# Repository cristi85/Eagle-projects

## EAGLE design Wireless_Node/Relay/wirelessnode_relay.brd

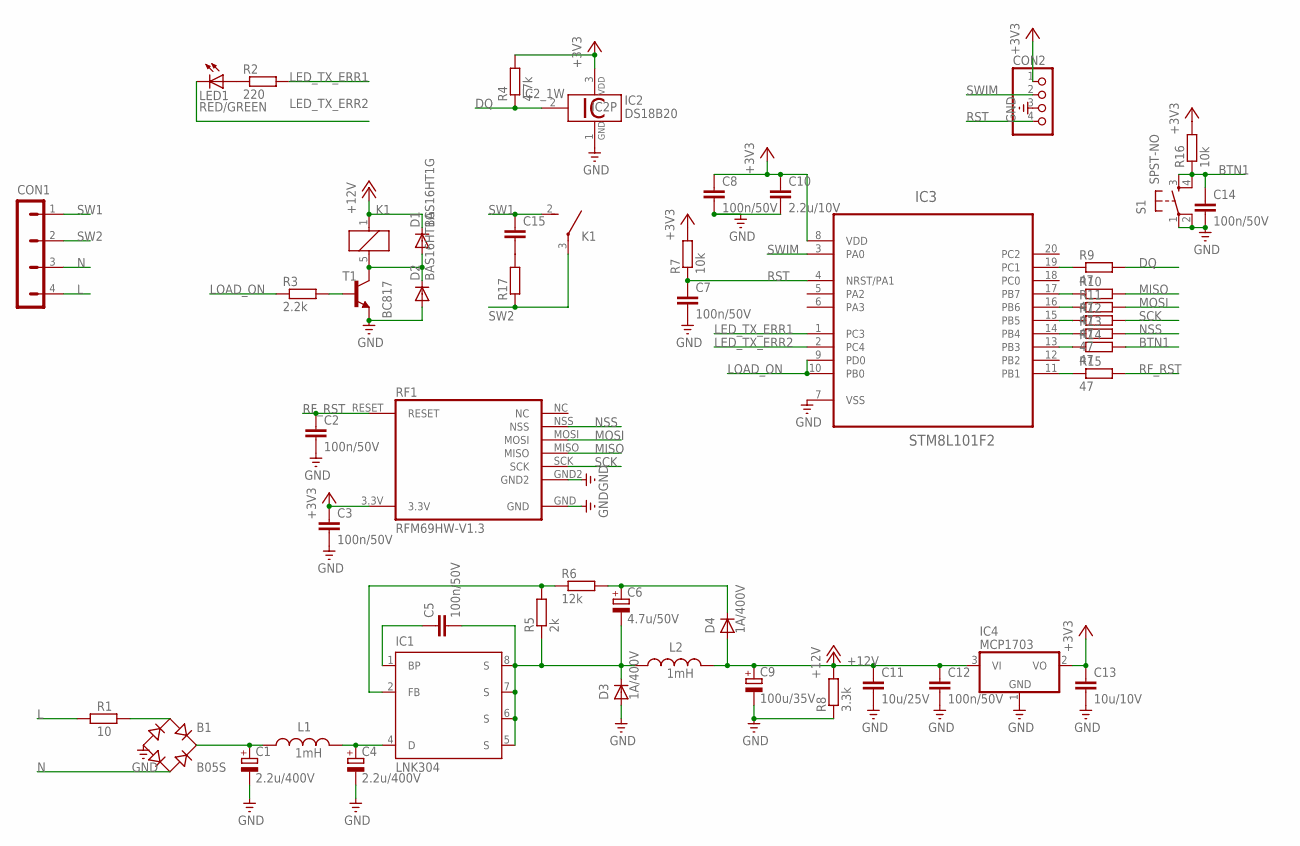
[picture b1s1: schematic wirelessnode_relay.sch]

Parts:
B1: B05S; MBS
C1, C4: 2.2u/400V; E3.5-8
C2, C3, C5, C7, C8, C12, C14: 100n/50V; C0603K
C6: 4.7u/50V; PANASONIC_C_LARGER_PADS
C9: 100u/35V; PANASONIC_D_LARGER_PADS
C10: 2.2u/10V; C0603K
C11: 10u/25V; C1206
C13: 10u/10V; C0603K
C15: C-EUC1812; C1812
CON1: POWER_CONN_4; TERMINAL_BLOCK_4
CON2: ZL321-4P; CON_1X4_1.27_SMD
D1, D2: BAS16HT1G; SOD323-W
D3: 1A/400V; DO214-AC
D4: 1A/400V; SOD-123F
IC1: LNK304; SO8_NO_PIN3
IC2: DS18B20; TO92-
IC3: STM8L101F2; TSSOP20
IC4: MCP1703; SOT23
K1: G5Q-1A4-EU
L1, L2: 1mH; DE0703
LED1: RED/GREEN; LED5MM
R1: 10; CF1WS
R2: 220; R0603
R3: 2.2k; R0603
R4: 4.7k; R0603
R5: 2k; R0603
R6: 12k; R0603
R7, R16: 10k; R0603
R8: 3.3k; R0603
R9, R10, R11, R12, R13, R14, R15: 47; R0603
R17: R-EU_R2010; R2010
RF1: RFM69HW-V1.3; RFM69HW-V1.3-SMD
S1: SPST-NO; DTSM-63X-V-7MM_HEIGHT
T1: BC817; SOT23-BEC

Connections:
+3V3: C3.1, C8.1, C10.1, C13.1, CON2.1, IC2.3 (VDD), IC3.8 (VDD), IC4.2 (VO), R4.2, R7.2, R16.2, RF1.3.3V
+12V: C9.+, C11.1, C12.1, D1.C, D4.2 (A), IC4.3 (VI), K1.1, L2.P$2 (2), R8.2
BTN1: C14.1, R14.2, R16.1, S1.3 (S), S1.4 (S1)
DQ: IC2.2 (1W), R4.1, R9.2
GND: B1.-, C1.-, C2.2, C3.2, C4.-, C7.2, C8.2, C9.-, C10.2, C11.2, C12.2, C13.2, C14.2, CON2.3, D2.A, D3.A, IC2.1 (GND), IC3.7 (VSS), IC4.1 (GND), R8.1, RF1.GND, RF1.GND2, S1.1, S1.2 (P1), T1.E
L: CON1.4, R1.1
LED_TX_ERR1: IC3.1 (PC3), R2.2
LED_TX_ERR2: IC3.2 (PC4), LED1.K (C)
LOAD_ON: IC3.9 (PD0), IC3.10 (PB0), R3.1
MISO: R10.2, RF1.MISO
MOSI: R11.2, RF1.MOSI
N: B1.AC2, CON1.3
unnamed: C4.+, IC1.4 (D), L1.P$2 (2)
unnamed: LED1.A, R2.1
unnamed: C6.+, D4.1 (C), R6.2
unnamed: IC1.2 (FB), R5.2, R6.1
unnamed: C5.1, IC1.1 (BP)
unnamed: C5.2, C6.-, D3.C, IC1.5 (S), IC1.6 (S), IC1.7 (S), IC1.8 (S), L2.P$1 (1), R5.1
unnamed: B1.AC1, R1.2
unnamed: D1.A, D2.C, K1.5 (2), T1.C
unnamed: IC3.14 (PB4), R13.1
unnamed: B1.+, C1.+, L1.P$1 (1)
unnamed: R3.2, T1.B
unnamed: C15.2, R17.2
unnamed: IC3.15 (PB5), R12.1
unnamed: IC3.16 (PB6), R11.1
unnamed: IC3.17 (PB7), R10.1
unnamed: IC3.11 (PB1), R15.1
unnamed: IC3.13 (PB3), R14.1
unnamed: IC3.19 (PC1), R9.1
NSS: R13.2, RF1.NSS
RF_RST: C2.1, R15.2, RF1.RESET
RST: C7.1, CON2.4, IC3.4 (NRST/PA1), R7.1
SCK: R12.2, RF1.SCK
SW1: C15.1, CON1.1, K1.2 (S)
SW2: CON1.2, K1.3, R17.1
SWIM: CON2.2, IC3.3 (PA0)

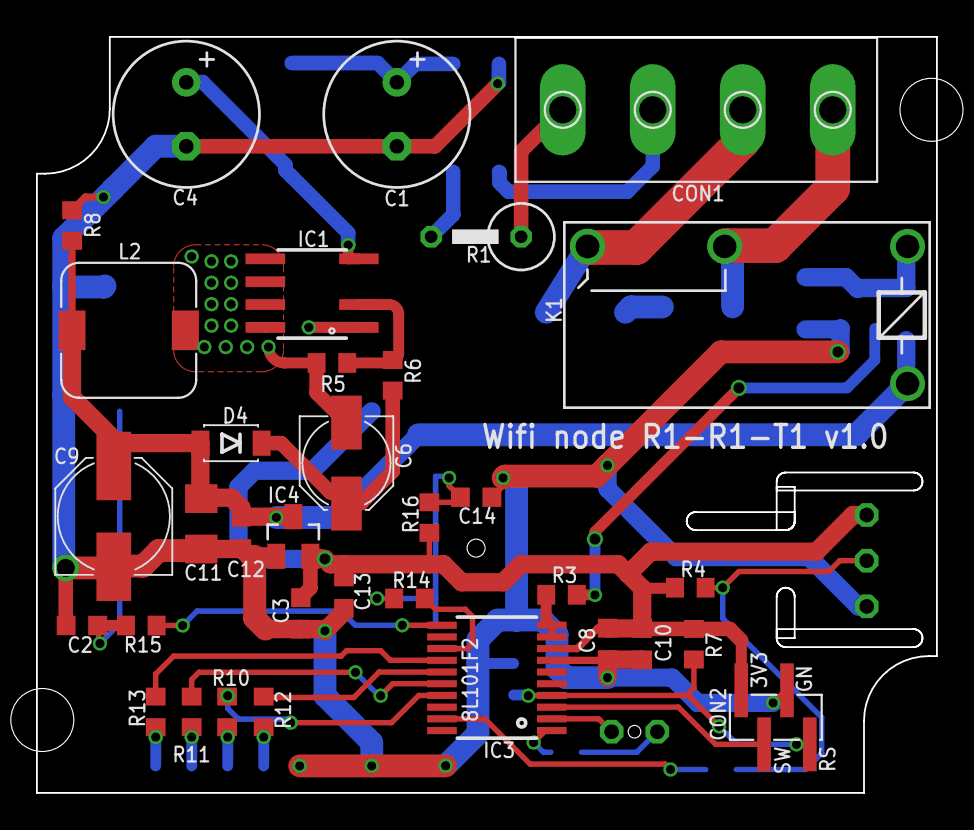
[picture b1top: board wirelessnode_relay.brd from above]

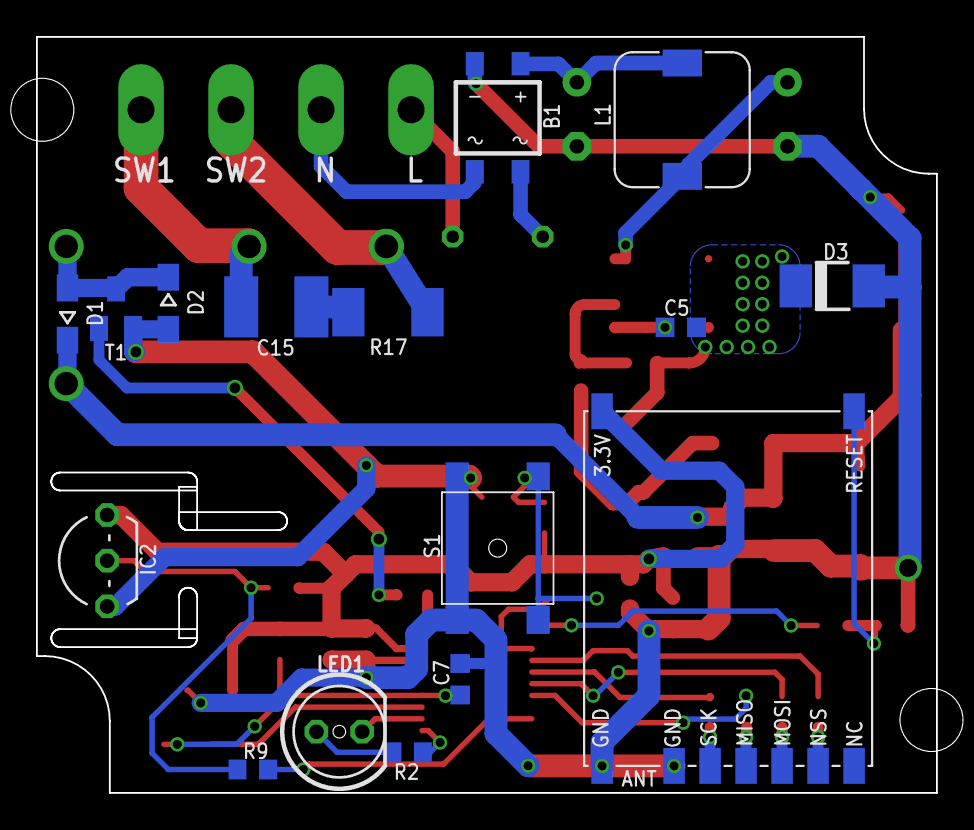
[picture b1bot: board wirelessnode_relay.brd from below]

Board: 2 copper layers, 50.0 x 42.0 mm, 50 parts (16 on the bottom side), 37 nets.

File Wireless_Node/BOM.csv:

"Qty";"Value";"Device";"Package";"Parts";"Description";"MF";"MPN";"OC_FARNELL";"OC_NEWARK";"TME_ORDER_NUMBER";
"1";"";"POWER_CONN_4";"TERMINAL_BLOCK_4";"CON1";"";"";"";"";"";"EBBA-02-C-SS-BU";
"1";"10";"R_CF1WS";"CF1WS";"R1";"";"";"";"";"";"CF1WS-10R";
"7";"100n/50V";"C-EUC0603K";"C0603K";"C2, C3, C5, C7, C8, C12, C14";"CAPACITOR, European symbol";"";"";"";"";"C0603C104K5RAC";
"1";"100u/35V";"C-POL-EUPANASONIC_D";"PANASONIC_D_LARGER_PADS";"C9";"";"";"";"";"";"UCD1V101MCL6GS";
"2";"10k";"R-EU_R0603";"R0603";"R8, R16";"RESISTOR, European symbol";"";"";"";"";"";
"1";"10u/10V";"C-EUC0603K";"C0603K";"C13";"CAPACITOR, European symbol";"";"";"";"";"0603ZD106MAT2A";
"1";"10u/25V";"C-EUC1206";"C1206";"C11";"CAPACITOR, European symbol";"";"";"";"";"08053D106KAT2A";
"2";"1A/400V";"SL1G";"SOD-123F";"D1, D3";"";"";"";"";"";"SL1G-DIO";
"1";"1A/400V";"US1G-DIO";"DO214-AC";"D2";"";"";"";"";"";"US1G-DIO";
"2";"1mH";"FERROCORE_DE0703-1000";"DE0703";"L1, L2";"FERROCORE SMD Power Coil";"";"";"";"";"DE0703-1000";
"1";"2.2u/10V";"C-EUC0603K";"C0603K";"C10";"CAPACITOR, European symbol";"";"";"";"";"CL10A225KP8NNNC";
"1";"2.2u/400V";"C-POL-EUCAP_8X11.5_AIR";"CAP_8X11.5_AIR";"C1";"";"";"";"";"";"RD2G225M0811MBB";
"2";"220";"R-EU_R0603";"R0603";"R2, R3";"RESISTOR, European symbol";"";"";"";"";"";
"1";"2k";"R-EU_R0603";"R0603";"R6";"RESISTOR, European symbol";"";"";"";"";"RC0603FR-072K";
"1";"3.3k";"R-EU_R0603";"R0603";"R9";"RESISTOR, European symbol";"";"";"";"";"RC0603FR-073K3";
"2";"360";"R-EU_R0603";"R0603";"R4, R5";"RESISTOR, European symbol";"";"";"";"";"";
"1";"4.7u/400V";"C-POL-EUE5-10,5";"E5-10,5";"C4";"";"";"";"";"";"RD2G475M1012MBB";
"1";"4.7u/50V";"C-POL-EU";"PANASONIC_C_LARGER_PADS";"C6";"";"";"";"";"";"RC1H475M05005VR";
"6";"47";"R-EU_R0603";"R0603";"R10, R11, R12, R13, R14, R15";"RESISTOR, European symbol";"";"";"";"";"";
"1";"8.6K";"R-EU_R0603";"R0603";"R7";"RESISTOR, European symbol";"";"";"";"";"CRCW06038K66FKTABC ";
"1";"BTA16";"BT136SMD";"TO220_SMD";"T2";"";"";"";"";"";"BTA16-600BRG";
"1";"LNK304";"LNK304";"SO8_NO_PIN3";"IC1";"";"";"";"";"";"LNK304DN";
"1";"MCP1703";"MCP1703CB";"SOT23";"IC3";"250 mA, 16V, Low Quiescent Current LDO Regulator";"";"";"";"";"MCP1703T3302ECB";
"1";"RED/GREEN";"LED5MM";"LED5MM";"LED1";"LED";"";"";"";"";"L-57EGW";
"1";"RFM69HW-V1.3";"RFM69HW-V1.3";"RFM69HW-V1.3-SMD";"RF1";"";"";"";"";"";"RFM69HW-868S2";
"1";"SPST-NO";"DTSM-63X-V";"DTSM-63X-V-7MM_HEIGHT";"S1";"";"";"";"";"";"DTSM-63N-V-B";
"1";"STM8L101F2";"STM8L101F2";"TSSOP20";"IC2";"";"";"";"";"";"STM8L101F2P6";
"1";"VO3063-X007T";"MOC3042S";"DIL6-SMD";"T1";"6-Pin DIP Zero-Cross Optoisolators Triac Driver Output (250/400 Volt Peak)";"FAIRCHILD SEMICONDUCTOR";"MOC3042SM";"unknown";"34C1339";"VO3063-X007T";
"1";"ZL321-4P";"CON_1X4PIN_1.27MM_SMD";"CON_1X4_1.27_SMD";"CON2";"";"";"";"";"";"ZL321-4P (DS1065-01-1X4S8BV)";

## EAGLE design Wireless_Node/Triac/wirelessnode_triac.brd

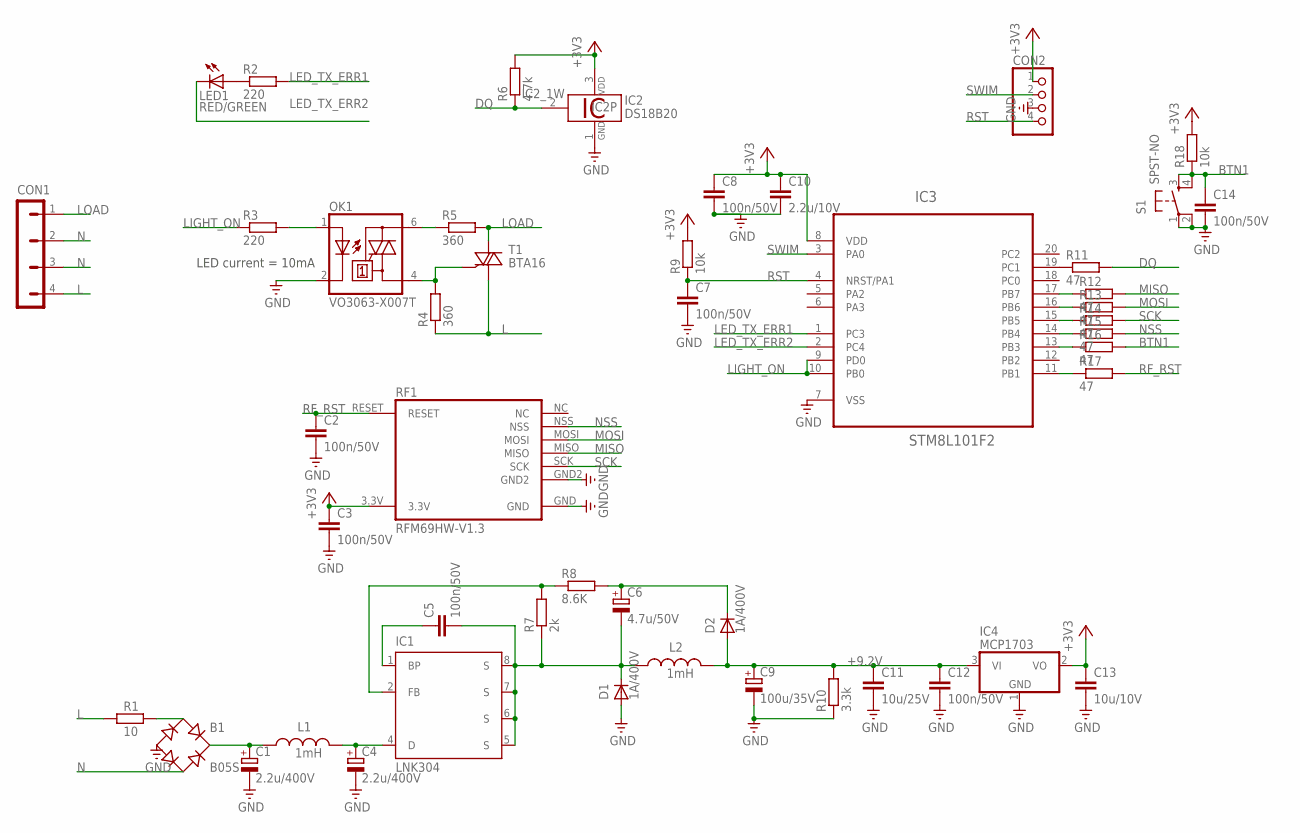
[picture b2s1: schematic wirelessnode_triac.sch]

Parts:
B1: B05S; MBS
C1, C4: 2.2u/400V; E3.5-8
C2, C3, C5, C7, C8, C12, C14: 100n/50V; C0603K
C6: 4.7u/50V; PANASONIC_C_LARGER_PADS
C9: 100u/35V; PANASONIC_D_LARGER_PADS
C10: 2.2u/10V; C0603K
C11: 10u/25V; C1206
C13: 10u/10V; C0603K
CON1: POWER_CONN_4; TERMINAL_BLOCK_4
CON2: ZL321-4P; CON_1X4_1.27_SMD
D1: 1A/400V; DO214-AC
D2: 1A/400V; SOD-123F
IC1: LNK304; SO8_NO_PIN3
IC2: DS18B20; TO92-
IC3: STM8L101F2; TSSOP20
IC4: MCP1703; SOT23
L1, L2: 1mH; DE0703
LED1: RED/GREEN; LED5MM
OK1: VO3063-X007T; DIL6-SMD
R1: 10; CF1WS
R2, R3: 220; R0603
R4, R5: 360; R0603
R6: 4.7k; R0603
R7: 2k; R0603
R8: 8.6K; R0603
R9, R18: 10k; R0603
R10: 3.3k; R0603
R11, R12, R13, R14, R15, R16, R17: 47; R0603
RF1: RFM69HW-V1.3; RFM69HW-V1.3-SMD
S1: SPST-NO; DTSM-63X-V-7MM_HEIGHT
T1: BTA16; TO220_SMD

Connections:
+3V3: C3.1, C8.1, C10.1, C13.1, CON2.1, IC2.3 (VDD), IC3.8 (VDD), IC4.2 (VO), R6.2, R9.2, R18.2, RF1.3.3V
+9.2V: C9.+, C11.1, C12.1, D2.2 (A), IC4.3 (VI), L2.P$2 (2), R10.2
BTN1: C14.1, R16.2, R18.1, S1.3 (S), S1.4 (S1)
DQ: IC2.2 (1W), R6.1, R11.2
GND: B1.-, C1.-, C2.2, C3.2, C4.-, C7.2, C8.2, C9.-, C10.2, C11.2, C12.2, C13.2, C14.2, CON2.3, D1.A, IC2.1 (GND), IC3.7 (VSS), IC4.1 (GND), OK1.2 (C), R10.1, RF1.GND, RF1.GND2, S1.1, S1.2 (P1)
L: CON1.4, R1.1, R4.1, T1.1 (A1)
LED_TX_ERR1: IC3.1 (PC3), R2.2
LED_TX_ERR2: IC3.2 (PC4), LED1.K (C)
LIGHT_ON: IC3.9 (PD0), IC3.10 (PB0), R3.1
LOAD: CON1.1, R5.2, T1.2 (A2)
MISO: R12.2, RF1.MISO
MOSI: R13.2, RF1.MOSI
N: B1.AC2, CON1.2, CON1.3
unnamed: C4.+, IC1.4 (D), L1.P$2 (2)
unnamed: LED1.A, R2.1
unnamed: C6.+, D2.1 (C), R8.2
unnamed: IC1.2 (FB), R7.2, R8.1
unnamed: C5.1, IC1.1 (BP)
unnamed: C5.2, C6.-, D1.C, IC1.5 (S), IC1.6 (S), IC1.7 (S), IC1.8 (S), L2.P$1 (1), R7.1
unnamed: OK1.6 (A2), R5.1
unnamed: OK1.4 (A1), R4.2, T1.3 (G)
unnamed: IC3.14 (PB4), R15.1
unnamed: B1.+, C1.+, L1.P$1 (1)
unnamed: OK1.1 (A), R3.2
unnamed: B1.AC1, R1.2
unnamed: IC3.15 (PB5), R14.1
unnamed: IC3.16 (PB6), R13.1
unnamed: IC3.17 (PB7), R12.1
unnamed: IC3.11 (PB1), R17.1
unnamed: IC3.13 (PB3), R16.1
unnamed: IC3.19 (PC1), R11.1
NSS: R15.2, RF1.NSS
RF_RST: C2.1, R17.2, RF1.RESET
RST: C7.1, CON2.4, IC3.4 (NRST/PA1), R9.1
SCK: R14.2, RF1.SCK
SWIM: CON2.2, IC3.3 (PA0)

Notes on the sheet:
LED current = 10mA

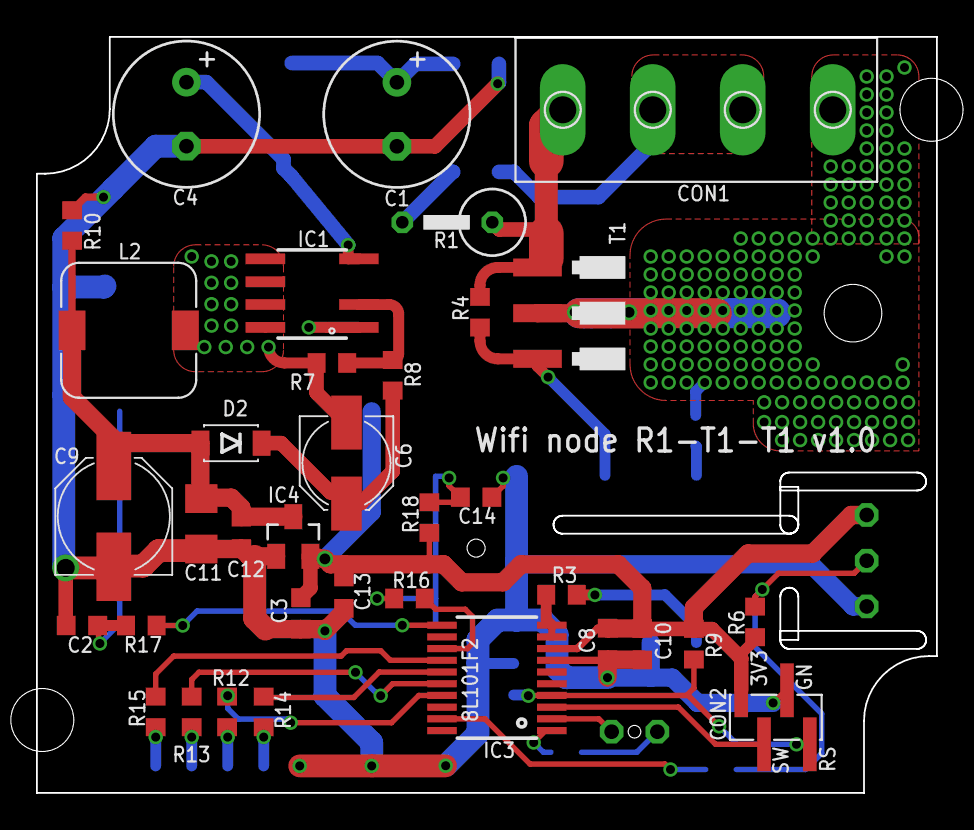
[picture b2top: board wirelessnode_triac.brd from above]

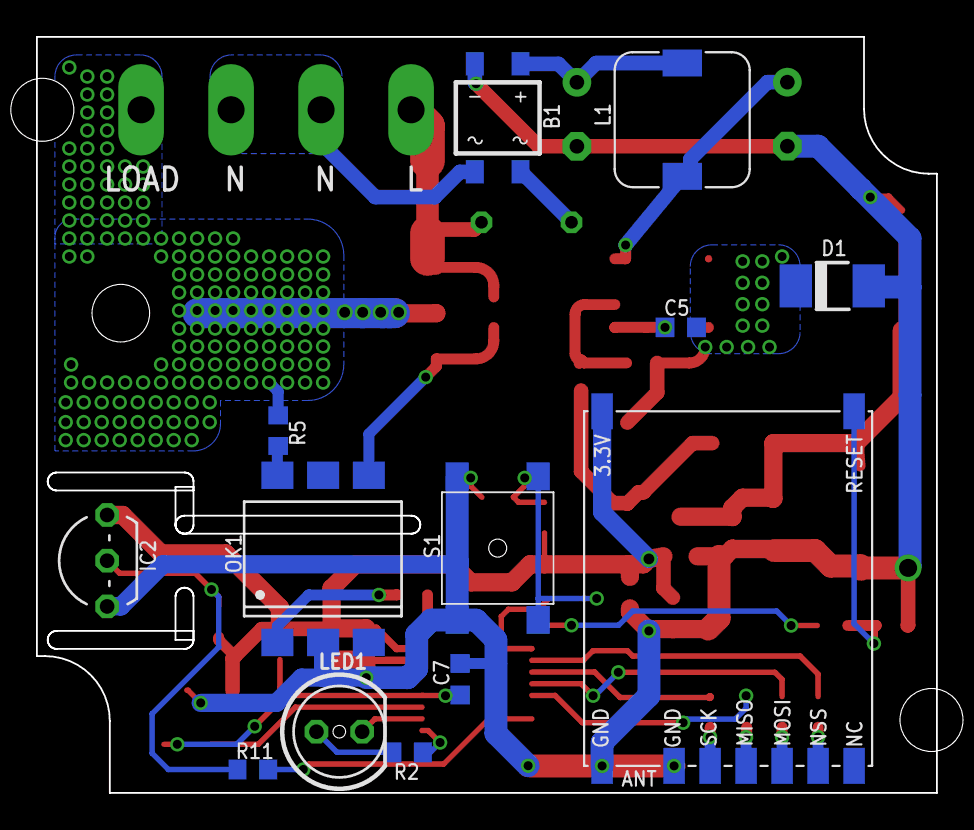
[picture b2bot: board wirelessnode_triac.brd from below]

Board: 2 copper layers, 50.0 x 42.0 mm, 48 parts (13 on the bottom side), 36 nets.

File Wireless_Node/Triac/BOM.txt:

Partlist exported from D:/_WORK/GitHub/Eagle projects/Wireless_Node/wirelessnode.sch at 3/2/2016 4:11 PM

Qty Value        Device                 Package                 Parts                        Description                                                                MF                      MPN       OC_FARNELL OC_NEWARK TME_ORDER_NUMBER            
1                POWER_CONN_4           TERMINAL_BLOCK_4        CON1                                                                                                                                                           EBBA-02-C-SS-BU             
1   10           R_CF1WS                CF1WS                   R1                                                                                                                                                             CF1WS-10R                   
7   100n/50V     C-EUC0603K             C0603K                  C2, C3, C5, C7, C8, C12, C14 CAPACITOR, European symbol                                                                                                        C0603C104K5RAC              
1   100u/35V     C-POL-EUPANASONIC_D    PANASONIC_D_LARGER_PADS C9                                                                                                                                                             UCD1V101MCL6GS              
2   10k          R-EU_R0603             R0603                   R8, R16                      RESISTOR, European symbol                                                                                                                                     
1   10u/25V      C-EUC1206              C1206                   C11                          CAPACITOR, European symbol                                                                                                        08053D106KAT2A              
1   10u/6.3V     C-EUC0603K             C0603K                  C13                          CAPACITOR, European symbol                                                                                                        CL10A106KQ8NNNC             
2   1A/400V      SL1G                   SOD-123F                D1, D3                                                                                                                                                         SL1G-DIO                    
1   1A/400V      US1G-DIO               DO214-AC                D2                                                                                                                                                             US1G-DIO                    
2   1mH          FERROCORE_DE0703-1000  DE0703                  L1, L2                       FERROCORE SMD Power Coil                                                                                                          DE0703-1000                 
1   2.2u/10V     C-EUC0603K             C0603K                  C10                          CAPACITOR, European symbol                                                                                                        CL10A225KP8NNNC             
1   2.2u/400V    C-POL-EUCAP_8X11.5_AIR CAP_8X11.5_AIR          C1                                                                                                                                                             RD2G225M0811MBB             
2   220          R-EU_R0603             R0603                   R2, R3                       RESISTOR, European symbol                                                                                                                                     
1   2k           R-EU_R0603             R0603                   R6                           RESISTOR, European symbol                                                                                                                                     
1   3.3k         R-EU_R0603             R0603                   R9                           RESISTOR, European symbol                                                                                                                                     
2   360          R-EU_R0603             R0603                   R4, R5                       RESISTOR, European symbol                                                                                                                                     
1   4.7u/400V    C-POL-EUE5-10,5        E5-10,5                 C4                                                                                                                                                             RD2G475M1012MBB             
1   4.7u/50V     C-POL-EU               PANASONIC_C_LARGER_PADS C6                                                                                                                                                             RC1H475M05005VR             
6   47           R-EU_R0603             R0603                   R10, R11, R12, R13, R14, R15 RESISTOR, European symbol                                                                                                                                     
1   8.6K         R-EU_R0603             R0603                   R7                           RESISTOR, European symbol                                                                                                                                     
1   BTA16        BT136                  TO220                   T2                                                                                                                                                             BTA16-600BRG                
1   LNK304       LNK304                 SO8_NO_PIN3             IC1                                                                                                                                                            LNK304DN                    
1   MCP1703      MCP1703CB              SOT23                   IC3                          250 mA, 16V, Low Quiescent Current LDO Regulator                                                                                  MCP1703T3302ECB             
1   MOC3063XSM   MOC3042S               DIL6-SMD                T1                           6-Pin DIP Zero-Cross Optoisolators Triac Driver Output (250/400 Volt Peak) FAIRCHILD SEMICONDUCTOR MOC3042SM unknown    34C1339   MOC3063XSM                  
1   RED/GREEN    LED5MM                 LED5MM                  LED1                         LED                                                                                                                               L-57EGW                     
1   RFM69HW-V1.3 RFM69HW-V1.3           RFM69HW-V1.3-SMD        RF1                                                                                                                                                            RFM69HW-868S2               
1   SPST-NO      DTSM-63X-V             DTSM-63X-V-7MM_HEIGHT   S1                                                                                                                                                             DTSM-63N-V-B                
1   STM8L101F2   STM8L101F2             TSSOP20                 IC2                                                                                                                                                            STM8L101F2P6                
1   ZL321-4P     CON_1X4PIN_1.27MM_SMD  CON_1X4_1.27_SMD        CON2                                                                                                                                                           ZL321-4P (DS1065-01-1X4S8BV)

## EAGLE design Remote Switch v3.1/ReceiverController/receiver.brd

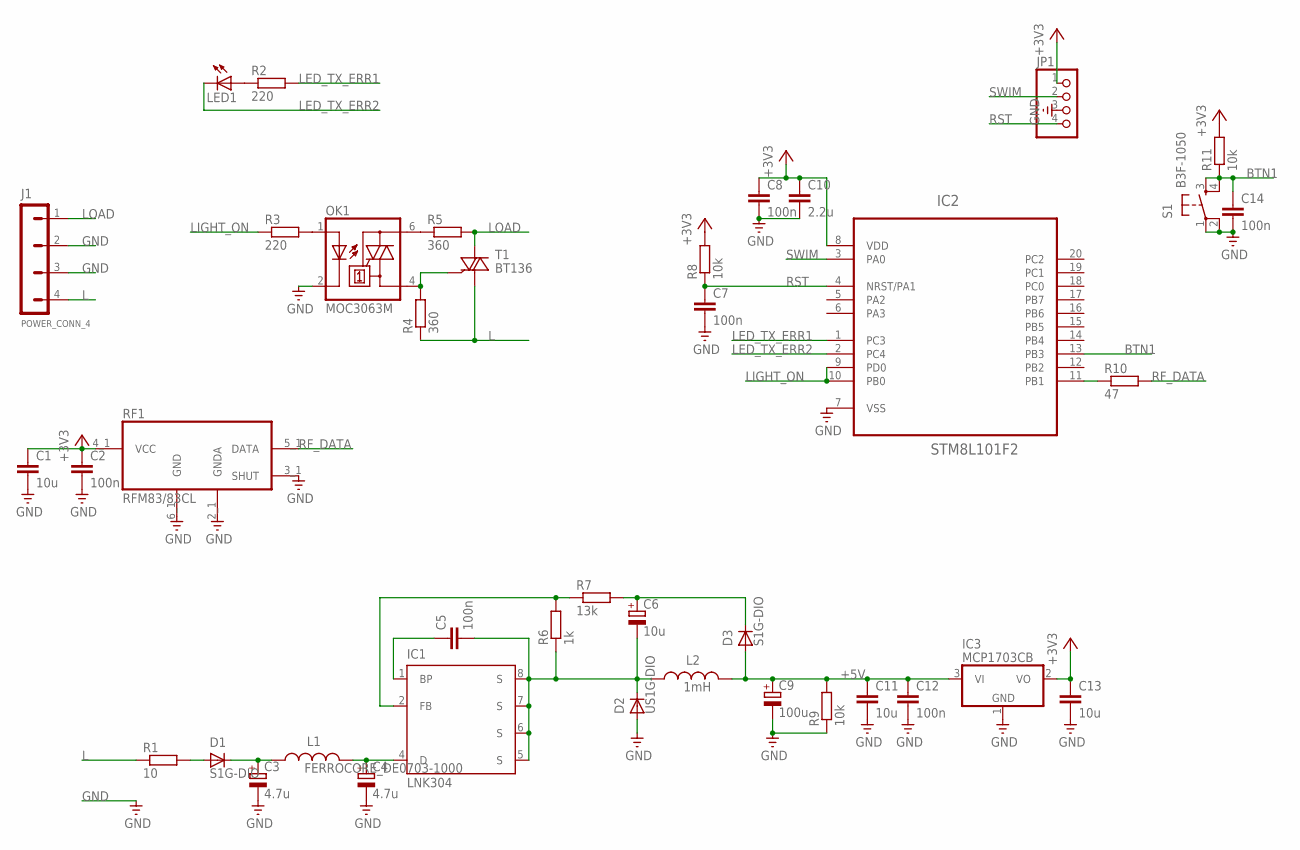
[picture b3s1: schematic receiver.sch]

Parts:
C1, C11, C13: 10u; C1206
C2, C5, C7, C8, C12, C14: 100n; C0603K
C3: 4.7u; CAP_10X12.5_AIR
C4: 4.7u; E5-10,5
C6: 10u; PANASONIC_C_LARGER_PADS
C9: 100u; PANASONIC_D_LARGER_PADS
C10: 2.2u; C1206
D1, D3: S1G-DIO; DO214-AC
D2: US1G-DIO; DO214-AC
IC1: LNK304; SO8_NO_PIN3
IC2: STM8L101F2; TSSOP20
IC3: MCP1703CB; SOT23
J1: POWER_CONN_4; TERMINAL_BLOCK_4
JP1: CON_1X4PIN_2.54MM_SMD; CON_1X4_2.54_SMD
L1: FERROCORE_DE0703-1000; DE0703
L2: 1mH; DE0703
LED1: LED3MM
OK1: MOC3063M; DIL06
R1: 10; R2512_LARGER_PADS
R2, R3: 220; R0603
R4, R5: 360; R0603
R6: 1k; R0603
R7: 13k; R0603
R8, R9, R11: 10k; R0603
R10: 47; R0603
RF1: RFM83/83CL; RFM83C/83CL_CONN
S1: B3F-1050; DTS-6
T1: BT136; TO220AB

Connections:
+3V3: C1.1, C2.1, C8.1, C10.1, C13.1, IC2.8 (VDD), IC3.2 (VO), JP1.1, R8.2, R11.2, RF1.4_1 (VCC)
+5V: C9.+, C11.1, C12.1, D3.A, IC3.3 (VI), L2.P$2 (2), R9.2
BTN1: C14.1, IC2.13 (PB3), R11.1, S1.3, S1.4
GND: C1.2, C2.2, C3.-, C4.-, C7.2, C8.2, C9.-, C10.2, C11.2, C12.2, C13.2, C14.2, D2.A, IC2.7 (VSS), IC3.1 (GND), J1.2, J1.3, JP1.3, OK1.2 (C), R9.1, RF1.2_1 (GNDA), RF1.3_1 (SHUT), RF1.6_1 (GND), S1.1, S1.2
L: J1.4, R1.1, R4.1, T1.1 (A1)
LED_TX_ERR1: IC2.1 (PC3), R2.2
LED_TX_ERR2: IC2.2 (PC4), LED1.K (C)
LIGHT_ON: IC2.9 (PD0), IC2.10 (PB0), R3.1
LOAD: J1.1, R5.2, T1.2 (A2)
unnamed: C4.+, IC1.4 (D), L1.P$2 (2)
unnamed: LED1.A, R2.1
unnamed: C6.+, D3.C, R7.2
unnamed: IC1.2 (FB), R6.2, R7.1
unnamed: C5.1, IC1.1 (BP)
unnamed: C5.2, C6.-, D2.C, IC1.5 (S), IC1.6 (S), IC1.7 (S), IC1.8 (S), L2.P$1 (1), R6.1
unnamed: OK1.6 (A2), R5.1
unnamed: OK1.4 (A1), R4.2, T1.3 (G)
unnamed: IC2.11 (PB1), R10.1
unnamed: C3.+, D1.C, L1.P$1 (1)
unnamed: OK1.1 (A), R3.2
unnamed: D1.A, R1.2
RF_DATA: R10.2, RF1.5_1 (DATA)
RST: C7.1, IC2.4 (NRST/PA1), JP1.4, R8.1
SWIM: IC2.3 (PA0), JP1.2

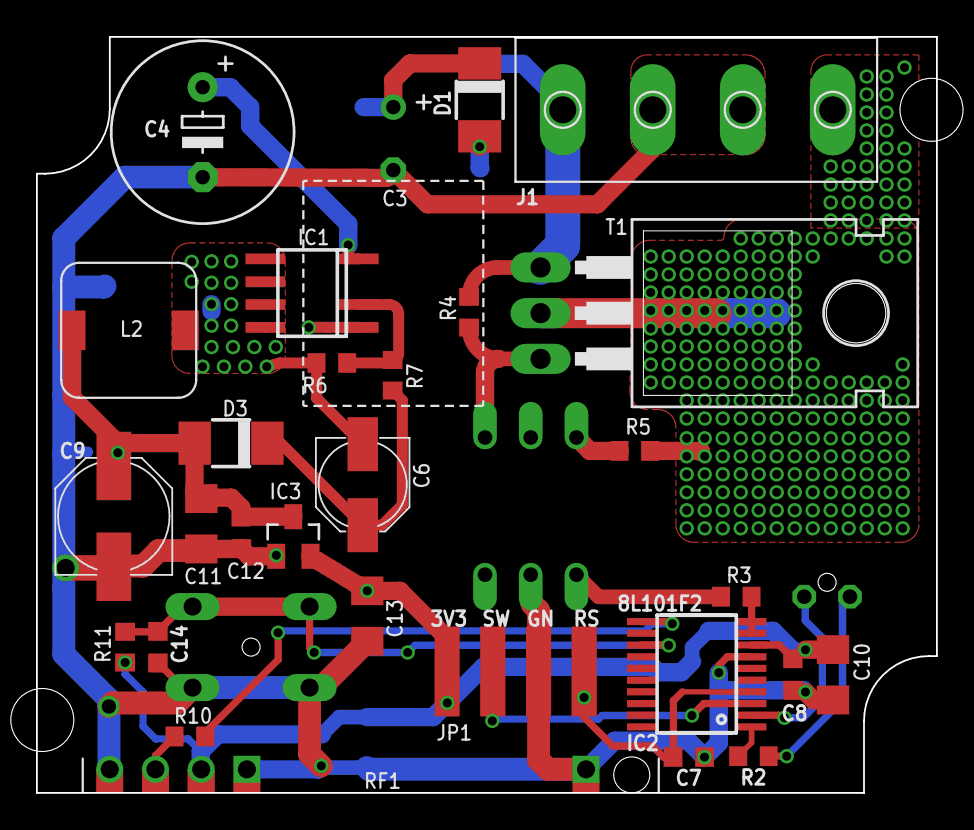
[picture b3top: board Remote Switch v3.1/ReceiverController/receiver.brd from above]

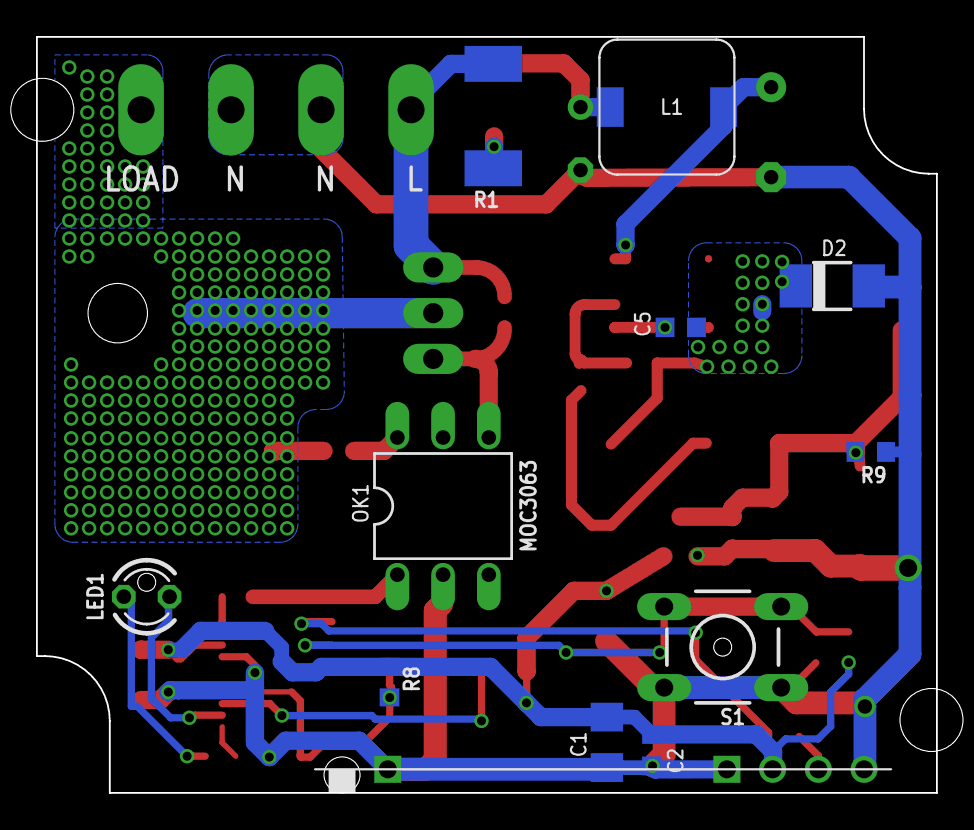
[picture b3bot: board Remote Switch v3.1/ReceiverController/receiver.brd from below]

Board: 2 copper layers, 50.0 x 42.0 mm, 40 parts (12 on the bottom side), 24 nets.

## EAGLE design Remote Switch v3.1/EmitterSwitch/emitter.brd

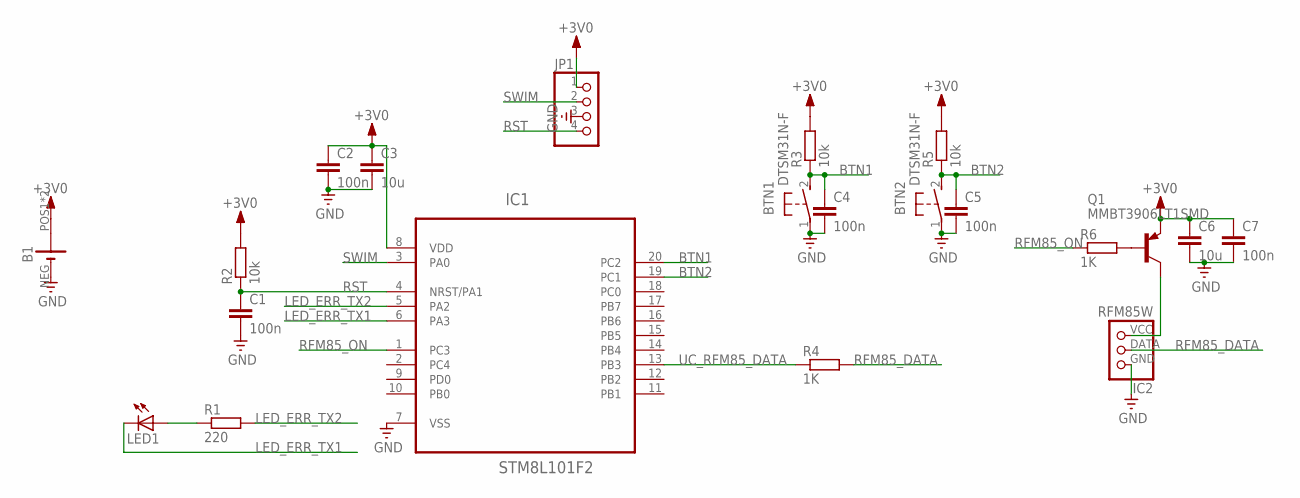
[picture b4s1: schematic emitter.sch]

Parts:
B1: CR2032_HOLDER_BC-2003
BTN1, BTN2: DTSM31N-F
C1, C2, C4, C5, C7: 100n; C0603K
C3, C6: 10u; C0805K
IC1: STM8L101F2; TSSOP20
IC2: RFM85W; RFM85W_CON
JP1: PINHD-1X4; 1X04
LED1: LED3MM
Q1: MMBT3906LT1SMD; SOT23-BEC
R1: 220; R0603
R2, R3, R5: 10k; R0603
R4, R6: 1K; R0603

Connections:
+3V0: B1.POS1 (+), B1.POS2 (+), C2.1, C3.1, C6.1, C7.1, IC1.8 (VDD), JP1.1, Q1.E, R2.2, R3.2, R5.2
BTN1: BTN1.2, C4.1, IC1.20 (PC2), R3.1
BTN2: BTN2.2, C5.1, IC1.19 (PC1), R5.1
GND: B1.NEG (-), BTN1.1, BTN2.1, C1.2, C2.2, C3.2, C4.2, C5.2, C6.2, C7.2, IC1.7 (VSS), IC2.GND (1), JP1.3
LED_ERR_TX1: IC1.6 (PA3), LED1.K (C)
LED_ERR_TX2: IC1.5 (PA2), R1.2
unnamed: LED1.A, R1.1
unnamed: IC2.VCC (3), Q1.C
unnamed: Q1.B, R6.2
RFM85_DATA: IC2.DATA (2), R4.2
RFM85_ON: IC1.1 (PC3), R6.1
RST: C1.1, IC1.4 (NRST/PA1), JP1.4, R2.1
SWIM: IC1.3 (PA0), JP1.2
UC_RFM85_DATA: IC1.13 (PB3), R4.1

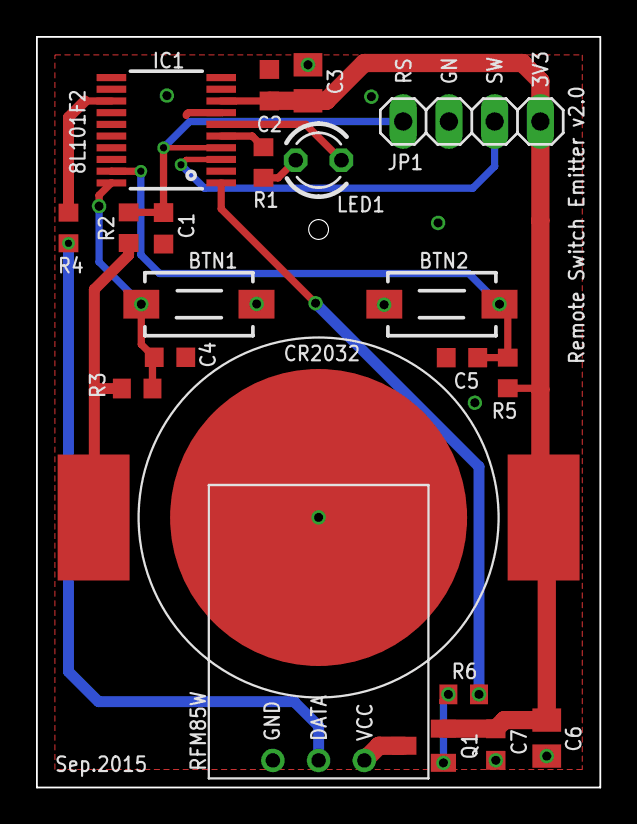
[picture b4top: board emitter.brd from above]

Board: 2 copper layers, 31.3 x 41.7 mm, 21 parts (0 on the bottom side), 14 nets.

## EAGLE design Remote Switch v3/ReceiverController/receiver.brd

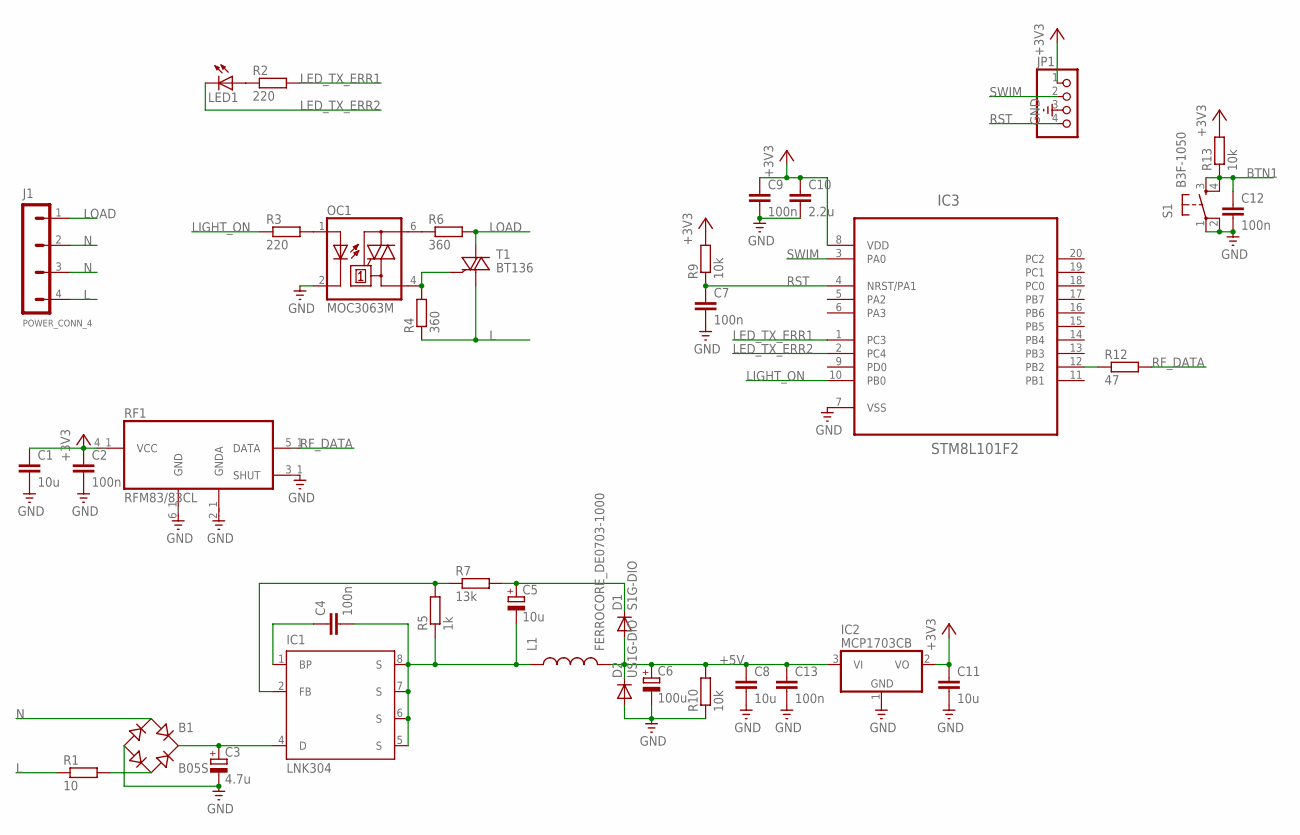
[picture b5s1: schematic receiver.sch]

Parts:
B1: B05S; MBS
C1, C8, C11: 10u; C0805K
C2, C4, C7, C9, C12, C13: 100n; C0603K
C3: 4.7u; E5-10,5
C5: 10u; PANASONIC_C
C6: 100u; PANASONIC_D
C10: 2.2u; C0805K
D1: S1G-DIO; DO214-AC
D2: US1G-DIO; DO214-AC
IC1: LNK304; SO8_NO_PIN3
IC2: MCP1703CB; SOT23
IC3: STM8L101F2; TSSOP20
J1: POWER_CONN_4; TERMINAL_BLOCK_4
JP1: PINHD-1X4; 1X04
L1: FERROCORE_DE0703-1000; DE0703
LED1: LED3MM
OC1: MOC3063M; DIL06
R1: 10; 0309/10
R2, R3: 220; R0603
R4, R6: 360; R0805
R5: 1k; R0603
R7: 13k; R0603
R9, R10, R13: 10k; R0603
R12: 47; R0603
RF1: RFM83/83CL; RFM83C/83CL_CONN
S1: B3F-1050; DTS-6
T1: BT136; TO220AB

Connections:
+3V3: C1.1, C2.1, C9.1, C10.1, C11.1, IC2.2 (VO), IC3.8 (VDD), JP1.1, R9.2, R13.2, RF1.4_1 (VCC)
+5V: C6.+, C8.1, C13.1, D1.A, D2.C, IC2.3 (VI), L1.P$2 (2), R10.2
BTN1: C12.1, R13.1, S1.3, S1.4
GND: B1.-, C1.2, C2.2, C3.-, C6.-, C7.2, C8.2, C9.2, C10.2, C11.2, C12.2, C13.2, D2.A, IC2.1 (GND), IC3.7 (VSS), JP1.3, OC1.2 (C), R10.1, RF1.2_1 (GNDA), RF1.3_1 (SHUT), RF1.6_1 (GND), S1.1, S1.2
L: J1.4, R1.1, R4.1, T1.1 (A1)
LED_TX_ERR1: IC3.1 (PC3), R2.2
LED_TX_ERR2: IC3.2 (PC4), LED1.K (C)
LIGHT_ON: IC3.10 (PB0), R3.1
LOAD: J1.1, R6.2, T1.2 (A2)
N: B1.AC1, J1.2, J1.3
unnamed: B1.+, C3.+, IC1.4 (D)
unnamed: LED1.A, R2.1
unnamed: C5.+, D1.C, R7.2
unnamed: IC1.2 (FB), R5.2, R7.1
unnamed: C4.1, IC1.1 (BP)
unnamed: C4.2, C5.-, IC1.5 (S), IC1.6 (S), IC1.7 (S), IC1.8 (S), L1.P$1 (1), R5.1
unnamed: OC1.6 (A2), R6.1
unnamed: OC1.4 (A1), R4.2, T1.3 (G)
unnamed: IC3.12 (PB2), R12.1
unnamed: B1.AC2, R1.2
unnamed: OC1.1 (A), R3.2
RF_DATA: R12.2, RF1.5_1 (DATA)
RST: C7.1, IC3.4 (NRST/PA1), JP1.4, R9.1
SWIM: IC3.3 (PA0), JP1.2

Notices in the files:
parts and their libraries:
supply1: Copyright (C) 2007, Bob Starr
